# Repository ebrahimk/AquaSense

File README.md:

# AquaSense

#### University of Zürich H2K Group and Oregon State University OPEnS Lab 
#### PI: Dr. Jan Seibert &  Dr.Ilja van Meerveld 
###### Team Leads: Kamron Ebrahimi, Jose Manuel Lopez Alcala

## About

AquaSense is a low-cost sensor system capable of measuring electrical conductivity (EC) and relative temperature (RT) of water streams. The device connects via Bluetooth to the AquaSense App, available for Android and iOS, capable of displaying a live feed of collected data and remotely configuring the sampling interval of the device for time series of varying resolutions.

Its primary users are people who are considered “super users” of the CrowdWater platform, a citizen science project sponsored by the University of Zurich intended to collect hydrological data including water level, streamflow, and soil moisture. “Super users” are individuals with more experience with the data collection processes and long term use of the application. These individuals would be sent an AquaSense system that they could use while they are surveying water streams using the CrowdWater application. 

The primary uses are for water hydrological characterization of streams, but it can be used as a teaching tool for emerging hydrology students, as well. As a researcher, having a tool that helps characterize the stream very quickly is extremely beneficial as the hand calculations and lab equipment need for this characterization will be expedited by this instrument. One application, other than EC and RT, is the estimation of water flow based on the concentration of the conductivity over time. This kind of sampling is also crucial characterization for a stream and can be easily estimated using an AquaSense instrument. As a student, this instrument can be beneficial as a way to materialize the theory learned in the classroom. The AquaSense application also aims to have an educational version where only the minimal data is collected for characterization and the calculations are left as an exercise for the student. 
The principle on which AquaSense works is based on electrical conductivity as an indicator of the ion content of the water and thus affecting the water’s ability to conduct an electrical current. An ion’s conductivity is temperature-dependent and for that reason, the system must be calibrated to the temperature of the water that is being sampled or have a temperature sensor that compensates the electrical conductivity readings. AquaSense is equipped with a temperature sensor probe so that users do not have to worry about doing a temperature compensation while in the field. Only a two-point calibration is needed before starting and this is done by putting the probe in two solutions of known conductivity and the system does all the calculations to calibrate the probe to the proper level.

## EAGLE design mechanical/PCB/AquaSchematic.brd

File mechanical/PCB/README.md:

This folder contains the EAGLE files that were created for the PCB of the AquaSense.

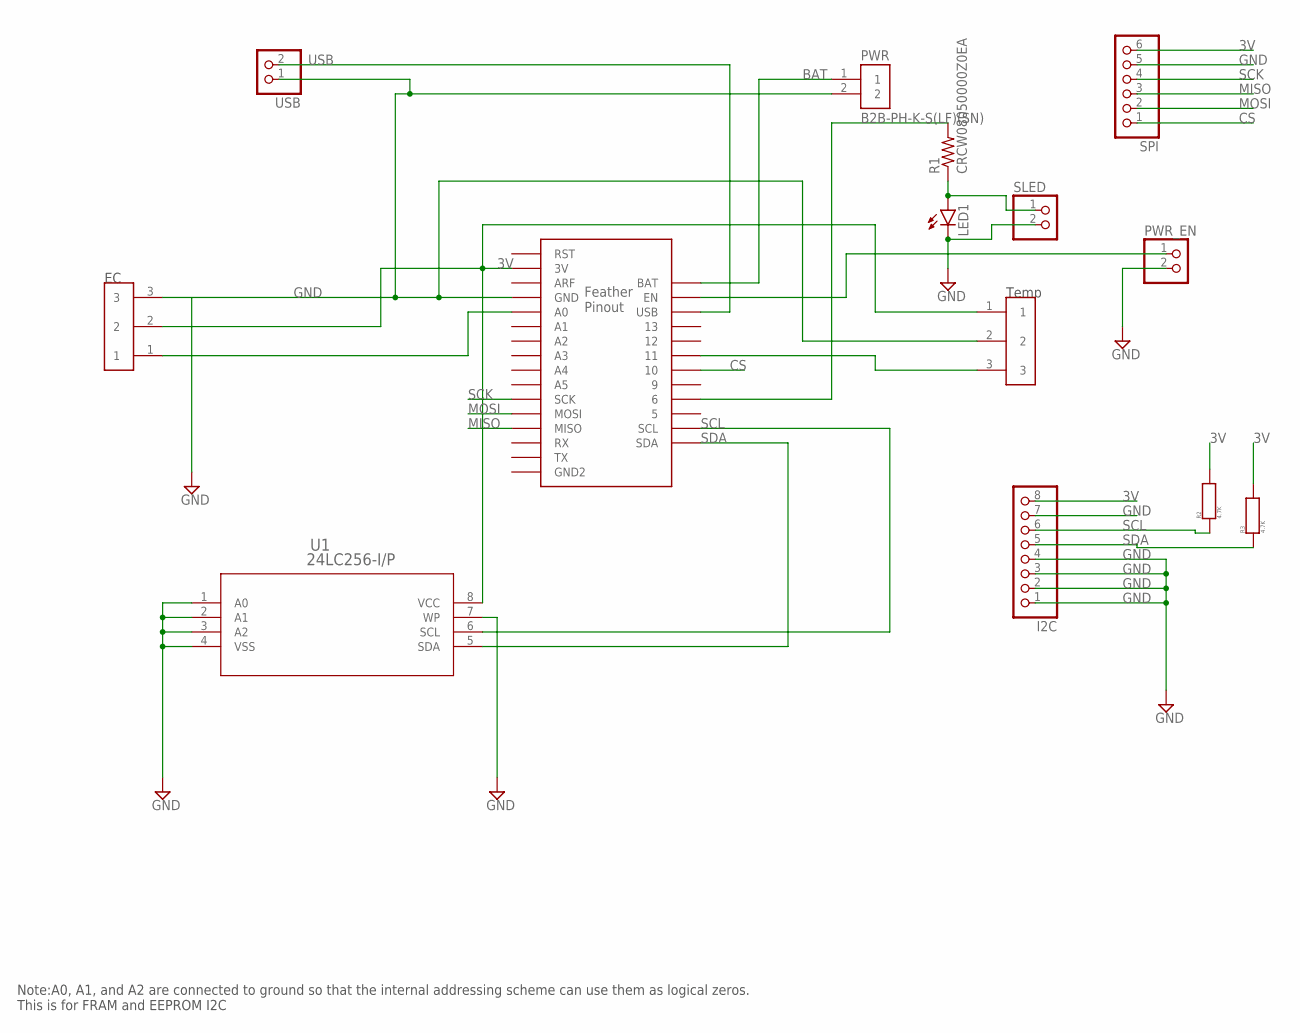
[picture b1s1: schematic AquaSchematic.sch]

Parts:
EC: 39773-0003
I2C: PINHD-1X8; 1X08
LED1: LEDCHIP-LED0805; CHIP-LED0805
PWR: B2B-PH-K-S(LF)(SN); JST_B2B-PH-K-S(LF)(SN)
PWR_EN: PINHD-1X2; 1X02
R1: CRCW08050000Z0EA; RES_0805
R2, R3: 4.7K; MFR3-4K7FC
SLED: PINHD-1X2; 1X02
SPI: PINHD-1X6; 1X06
TEMP: 39773-0003
U1: 24LC256-I/P; PDIP8_300MC
U$1: FEATHER_M0_PROTO; FEATHER_MO_PROTO
USB: PINHD-1X2; 1X02

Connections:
3V: EC.2, I2C.8, R2.PIN1, R3.PIN1, SPI.6, TEMP.1, U1.8 (VCC), U$1.3V
BAT: PWR.1, U$1.BAT
CS: SPI.1, U$1.10
EN: PWR_EN.1, U$1.EN
GND: EC.3, I2C.1, I2C.2, I2C.3, I2C.4, I2C.7, LED1.C, PWR.2, PWR_EN.2, SLED.2, SPI.5, TEMP.2, U1.1 (A0), U1.2 (A1), U1.3 (A2), U1.4 (VSS), U1.7 (WP), U$1.GND, USB.1
MISO: SPI.3, U$1.MISO
MOSI: SPI.2, U$1.MOSI
unnamed: LED1.A, R1.1, SLED.1
unnamed: R1.2, U$1.6
unnamed: EC.1, U$1.A0
unnamed: TEMP.3, U$1.11
SCK: SPI.4, U$1.SCK
SCL: I2C.6, R2.PIN2, U1.6 (SCL), U$1.SCL
SDA: I2C.5, R3.PIN2, U1.5 (SDA), U$1.SDA
USB: U$1.USB, USB.2

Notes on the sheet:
Note:A0, A1, and A2 are connected to ground so that the internal addressing scheme can use them as logical zeros. This is for FRAM and EEPROM I2C
Temp

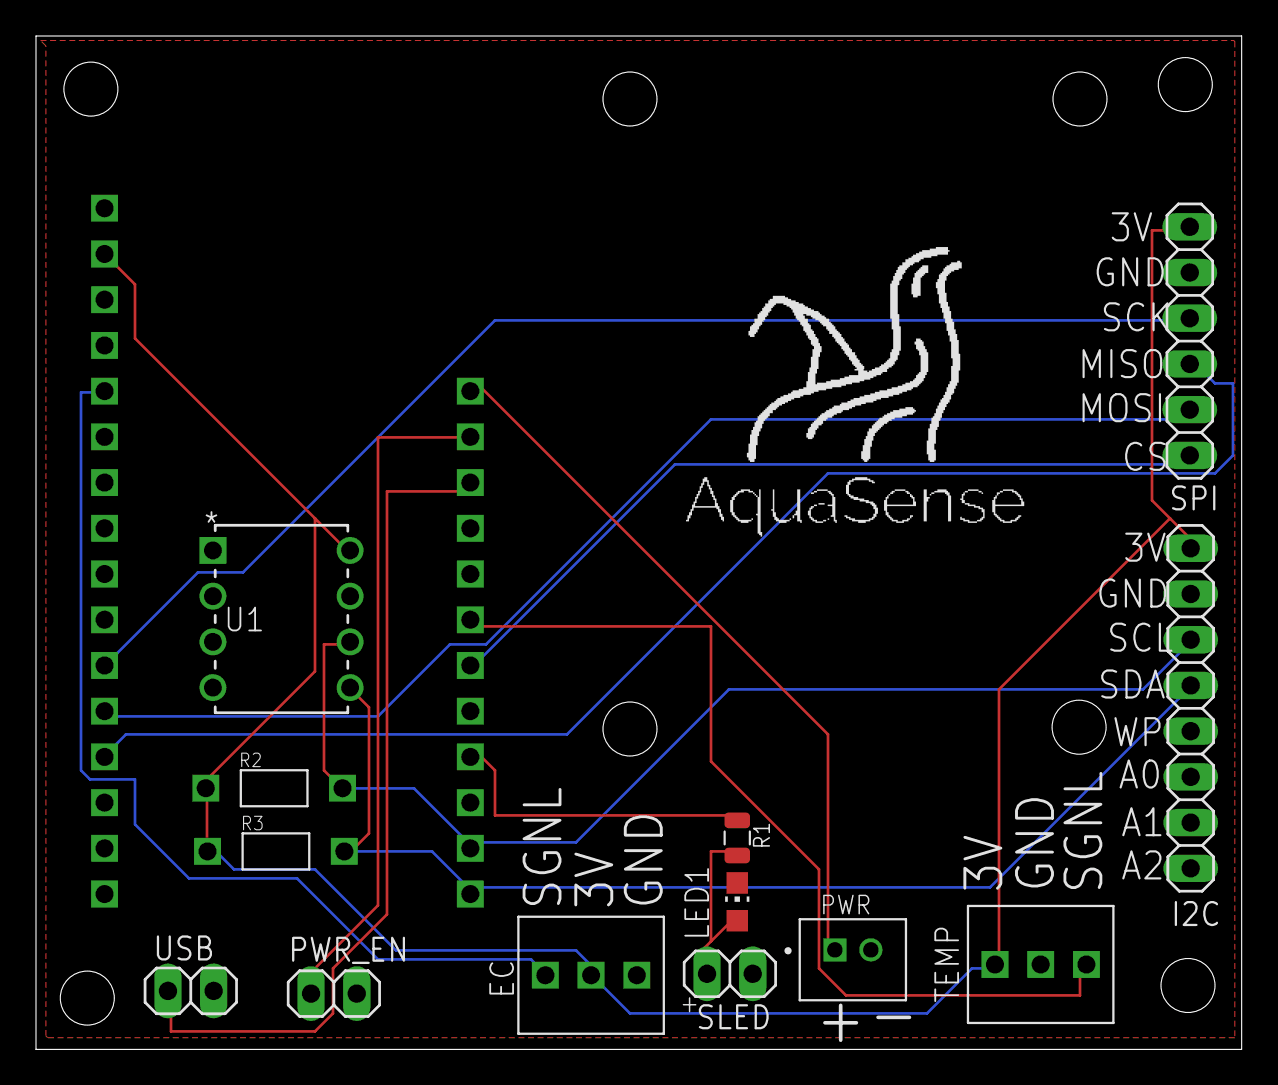
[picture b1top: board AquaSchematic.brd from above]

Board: 2 copper layers, 67.0 x 56.3 mm, 14 parts (0 on the bottom side), 15 nets.

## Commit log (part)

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2019-08-11 setting up bluetooth LE connection
2019-08-11 Ionic bluetooth LE connection working with nrf51822
2019-08-19 added temperature graph, formatted EC and temperature graphs, stop and start funcitonality
2019-08-19 added service for handling data routing between page navigation
2019-08-21 bi-directional communication complete
2019-08-22 added checksums for packet updates
2019-08-25 implemented 16 bit checksums tested up to 20 ms update rate, and wired all user input to Arduino
2019-08-26 selectable data point readouts implemented
2019-08-27 fixed stopwatch bug, and inaccurate timestamps
2019-08-27 reconfigured filepaths
2019-08-27 change target path in config.yml
2019-08-27 changed paths
2019-08-27 fixed some small bugs
2019-08-27 AquaSense can now log datafiles to internal storage
2019-08-28 added a menu with all log files
2019-08-29 logging and displaying logs complete, must implement deleting logs and navigation to logging from a live graph feed
2019-08-29 loading data feature
2019-08-29 app is almost complete
2019-08-30 AquaSense is done
2019-08-30 added mechanical file, working on readme
2019-12-29 Bump handlebars from 4.1.2 to 4.5.3 in /AquaSense
    Bumps [handlebars](https://github.com/wycats/handlebars.js) from 4.1.2 to 4.5.3.
    - [Release notes](https://github.com/wycats/handlebars.js/releases)
    - [Changelog](https://github.com/wycats/handlebars.js/blob/master/release-notes.md)
    - [Commits](https://github.com/wycats/handlebars.js/compare/v4.1.2...v4.5.3)
2020-04-16 Bump https-proxy-agent from 2.2.2 to 2.2.4 in /AquaSense
    Bumps [https-proxy-agent](https://github.com/TooTallNate/node-https-proxy-agent) from 2.2.2 to 2.2.4.
    - [Release notes](https://github.com/TooTallNate/node-https-proxy-agent/releases)
    - [Commits](https://github.com/TooTallNate/node-https-proxy-agent/compare/2.2.2...2.2.4)
2020-06-07 Bump websocket-extensions from 0.1.3 to 0.1.4 in /AquaSense
    Bumps [websocket-extensions](https://github.com/faye/websocket-extensions-node) from 0.1.3 to 0.1.4.
    - [Release notes](https://github.com/faye/websocket-extensions-node/releases)
    - [Changelog](https://github.com/faye/websocket-extensions-node/blob/master/CHANGELOG.md)
    - [Commits](https://github.com/faye/websocket-extensions-node/compare/0.1.3...0.1.4)
2020-07-31 Bump elliptic from 6.5.0 to 6.5.3 in /AquaSense
    Bumps [elliptic](https://github.com/indutny/elliptic) from 6.5.0 to 6.5.3.
    - [Release notes](https://github.com/indutny/elliptic/releases)
    - [Commits](https://github.com/indutny/elliptic/compare/v6.5.0...v6.5.3)
2020-09-06 Bump handlebars from 4.1.2 to 4.7.6 in /AquaSense
    Bumps [handlebars](https://github.com/wycats/handlebars.js) from 4.1.2 to 4.7.6.
    - [Release notes](https://github.com/wycats/handlebars.js/releases)
    - [Changelog](https://github.com/handlebars-lang/handlebars.js/blob/master/release-notes.md)
    - [Commits](https://github.com/wycats/handlebars.js/compare/v4.1.2...v4.7.6)
2021-03-09 Bump elliptic from 6.5.0 to 6.5.4 in /AquaSense
    Bumps [elliptic](https://github.com/indutny/elliptic) from 6.5.0 to 6.5.4.
    - [Release notes](https://github.com/indutny/elliptic/releases)
    - [Commits](https://github.com/indutny/elliptic/compare/v6.5.0...v6.5.4)
2021-04-30 Bump ssri from 6.0.1 to 6.0.2 in /AquaSense
    Bumps [ssri](https://github.com/npm/ssri) from 6.0.1 to 6.0.2.
    - [Release notes](https://github.com/npm/ssri/releases)
    - [Changelog](https://github.com/npm/ssri/blob/v6.0.2/CHANGELOG.md)
    - [Commits](https://github.com/npm/ssri/compare/v6.0.1...v6.0.2)
2021-05-08 Bump handlebars from 4.1.2 to 4.7.7 in /AquaSense
    Bumps [handlebars](https://github.com/wycats/handlebars.js) from 4.1.2 to 4.7.7.
    - [Release notes](https://github.com/wycats/handlebars.js/releases)
    - [Changelog](https://github.com/handlebars-lang/handlebars.js/blob/master/release-notes.md)
    - [Commits](https://github.com/wycats/handlebars.js/compare/v4.1.2...v4.7.7)
2021-05-10 Bump lodash from 4.17.15 to 4.17.21 in /AquaSense
    Bumps [lodash](https://github.com/lodash/lodash) from 4.17.15 to 4.17.21.
    - [Release notes](https://github.com/lodash/lodash/releases)
    - [Commits](https://github.com/lodash/lodash/compare/4.17.15...4.17.21)
2021-05-12 Bump chart.js from 2.8.0 to 2.9.4 in /AquaSense
    Bumps [chart.js](https://github.com/chartjs/Chart.js) from 2.8.0 to 2.9.4.
    - [Release notes](https://github.com/chartjs/Chart.js/releases)
    - [Commits](https://github.com/chartjs/Chart.js/compare/v2.8.0...v2.9.4)
2021-05-27 Bump dns-packet from 1.3.1 to 1.3.4 in /AquaSense
    Bumps [dns-packet](https://github.com/mafintosh/dns-packet) from 1.3.1 to 1.3.4.
    - [Release notes](https://github.com/mafintosh/dns-packet/releases)
    - [Changelog](https://github.com/mafintosh/dns-packet/blob/master/CHANGELOG.md)
    - [Commits](https://github.com/mafintosh/dns-packet/compare/v1.3.1...v1.3.4)
2021-08-11 Bump path-parse from 1.0.6 to 1.0.7 in /AquaSense
    Bumps [path-parse](https://github.com/jbgutierrez/path-parse) from 1.0.6 to 1.0.7.
    - [Release notes](https://github.com/jbgutierrez/path-parse/releases)
    - [Commits](https://github.com/jbgutierrez/path-parse/commits/v1.0.7)
    ---
    updated-dependencies:
    - dependency-name: path-parse
2021-09-01 Bump tar from 4.4.8 to 4.4.19 in /AquaSense
    Bumps [tar](https://github.com/npm/node-tar) from 4.4.8 to 4.4.19.
    - [Release notes](https://github.com/npm/node-tar/releases)
    - [Changelog](https://github.com/npm/node-tar/blob/main/CHANGELOG.md)
    - [Commits](https://github.com/npm/node-tar/compare/v4.4.8...v4.4.19)
    ---
    updated-dependencies:
2022-01-13 Bump follow-redirects from 1.7.0 to 1.14.7 in /AquaSense
    Bumps [follow-redirects](https://github.com/follow-redirects/follow-redirects) from 1.7.0 to 1.14.7.
    - [Release notes](https://github.com/follow-redirects/follow-redirects/releases)
    - [Commits](https://github.com/follow-redirects/follow-redirects/compare/v1.7.0...v1.14.7)
    ---
    updated-dependencies:
    - dependency-name: follow-redirects
2022-02-12 Bump follow-redirects from 1.7.0 to 1.14.8 in /AquaSense
    Bumps [follow-redirects](https://github.com/follow-redirects/follow-redirects) from 1.7.0 to 1.14.8.
    - [Release notes](https://github.com/follow-redirects/follow-redirects/releases)
    - [Commits](https://github.com/follow-redirects/follow-redirects/compare/v1.7.0...v1.14.8)
    ---
    updated-dependencies:
    - dependency-name: follow-redirects
2022-02-18 Bump url-parse from 1.4.7 to 1.5.7 in /AquaSense
    Bumps [url-parse](https://github.com/unshiftio/url-parse) from 1.4.7 to 1.5.7.
    - [Release notes](https://github.com/unshiftio/url-parse/releases)
    - [Commits](https://github.com/unshiftio/url-parse/compare/1.4.7...1.5.7)
    ---
    updated-dependencies:
    - dependency-name: url-parse
2022-03-02 Bump plist from 3.0.1 to 3.0.4 in /AquaSense
    Bumps [plist](https://github.com/TooTallNate/node-plist) from 3.0.1 to 3.0.4.
    - [Release notes](https://github.com/TooTallNate/node-plist/releases)
    - [Changelog](https://github.com/TooTallNate/plist.js/blob/master/History.md)
    - [Commits](https://github.com/TooTallNate/node-plist/commits)
    ---
    updated-dependencies:
2022-03-02 Bump karma from 4.1.0 to 6.3.16 in /AquaSense
    Bumps [karma](https://github.com/karma-runner/karma) from 4.1.0 to 6.3.16.
    - [Release notes](https://github.com/karma-runner/karma/releases)
    - [Changelog](https://github.com/karma-runner/karma/blob/master/CHANGELOG.md)
    - [Commits](https://github.com/karma-runner/karma/compare/v4.1.0...v6.3.16)
    ---
    updated-dependencies:
2022-06-01 Bump eventsource from 1.0.7 to 1.1.1 in /AquaSense
    Bumps [eventsource](https://github.com/EventSource/eventsource) from 1.0.7 to 1.1.1.
    - [Release notes](https://github.com/EventSource/eventsource/releases)
    - [Changelog](https://github.com/EventSource/eventsource/blob/master/HISTORY.md)
    - [Commits](https://github.com/EventSource/eventsource/compare/v1.0.7...v1.1.1)
    ---
    updated-dependencies:
2022-07-07 Bump moment from 2.24.0 to 2.29.4 in /AquaSense
    Bumps [moment](https://github.com/moment/moment) from 2.24.0 to 2.29.4.
    - [Release notes](https://github.com/moment/moment/releases)
    - [Changelog](https://github.com/moment/moment/blob/develop/CHANGELOG.md)
    - [Commits](https://github.com/moment/moment/compare/2.24.0...2.29.4)
    ---
    updated-dependencies:
2022-07-20 Bump terser from 4.1.3 to 4.8.1 in /AquaSense
    Bumps [terser](https://github.com/terser/terser) from 4.1.3 to 4.8.1.
    - [Release notes](https://github.com/terser/terser/releases)
    - [Changelog](https://github.com/terser/terser/blob/master/CHANGELOG.md)
    - [Commits](https://github.com/terser/terser/commits)
    ---
    updated-dependencies:
2022-09-26 Bump degenerator and @capacitor/cli in /AquaSense
    Removes [degenerator](https://github.com/TooTallNate/node-degenerator). It's no longer used after updating ancestor dependency [@capacitor/cli](https://github.com/ionic-team/capacitor). These depende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
    Removes `degenerator`
    Updates `@capacitor/cli` from 1.1.1 to 1.5.3
    - [Release notes](https://github.com/ionic-team/capacitor/releases)
    - [Changelog](https://github.com/ionic-team/capacitor/blob/main/CHANGELOG.md)
    - [Commits](https://github.com/ionic-team/capacitor/compare/1.1.1...1.5.3)
2022-10-29 Bump socket.io-parser and karma in /AquaSense
    Bumps [socket.io-parser](https://github.com/socketio/socket.io-parser) to 4.2.1 and updates ancestor dependency [karma](https://github.com/karma-runner/karma). These dependencies need to be updated t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
    Updates `socket.io-parser` from 3.2.0 to 4.2.1
    - [Release notes](https://github.com/socketio/socket.io-parser/releases)
    - [Changelog](https://github.com/socketio/socket.io-parser/blob/main/CHANGELOG.md)
    - [Commits](https://github.com/socketio/socket.io-parser/compare/3.2.0...4.2.1)
    Updates `karma` from 4.1.0 to 6.4.1
2022-11-18 Bump loader-utils and @angular-devkit/build-angular in /AquaSense
    Bumps [loader-utils](https://github.com/webpack/loader-utils) to 3.2.1 and updates ancestor dependency [@angular-devkit/build-angular](https://github.com/angular/angular-cli). These dependencies need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
    Updates `loader-utils` from 1.2.3 to 3.2.1
    - [Release notes](https://github.com/webpack/loader-utils/releases)
    - [Changelog](https://github.com/webpack/loader-utils/blob/master/CHANGELOG.md)
    - [Commits](https://github.com/webpack/loader-utils/compare/v1.2.3...v3.2.1)
    Updates `@angular-devkit/build-angular` from 0.801.3 to 15.0.0
2022-12-04 Bump decode-uri-component from 0.2.0 to 0.2.2 in /AquaSense
    Bumps [decode-uri-component](https://github.com/SamVerschueren/decode-uri-component) from 0.2.0 to 0.2.2.
    - [Release notes](https://github.com/SamVerschueren/decode-uri-component/releases)
    - [Commits](https://github.com/SamVerschueren/decode-uri-component/compare/v0.2.0...v0.2.2)
    ---
    updated-dependencies:
    - dependency-name: decode-uri-component
2022-12-09 Bump qs from 6.5.2 to 6.5.3 in /AquaSense
    Bumps [qs](https://github.com/ljharb/qs) from 6.5.2 to 6.5.3.
    - [Release notes](https://github.com/ljharb/qs/releases)
    - [Changelog](https://github.com/ljharb/qs/blob/main/CHANGELOG.md)
    - [Commits](https://github.com/ljharb/qs/compare/v6.5.2...v6.5.3)
    ---
    updated-dependencies:
2023-01-01 Bump json5 and @angular-devkit/build-angular in /AquaSense
    Bumps [json5](https://github.com/json5/json5) to 2.2.3 and updates ancestor dependency [@angular-devkit/build-angular](https://github.com/angular/angular-cli). These dependencies need to be updated t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
    Updates `json5` from 1.0.1 to 2.2.3
    - [Release notes](https://github.com/json5/json5/releases)
    - [Changelog](https://github.com/json5/json5/blob/main/CHANGELOG.md)
    - [Commits](https://github.com/json5/json5/compare/v1.0.1...v2.2.3)
    Updates `@angular-devkit/build-angular` from 0.801.3 to 15.0.4
